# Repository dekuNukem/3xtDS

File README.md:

3xtDS
=====

The 3DS Streaming Console with External Control Interface, or 3xtDS, is a modified Nintendo 3DS console equipped with an capture card and an USB interface that allows the control of buttons, circle pad, and touch screen from an external source, as well as streaming high quality video of the content of both screen and sound back to the host to be recorded, or broadcast. This allows some very interesting applications such as interactive streaming on Twitch or other websites, gameplay automation, remote play over Internet, using alternative controllers, and much more.

Please see a short video of it in action: https://www.youtube.com/watch?v=9PZrJH7Z8KE

I want to thank u/velocikoopa for providing a console for me to work on, without him this project would be impossible.

Project gallery: http://imgur.com/a/ICxh5

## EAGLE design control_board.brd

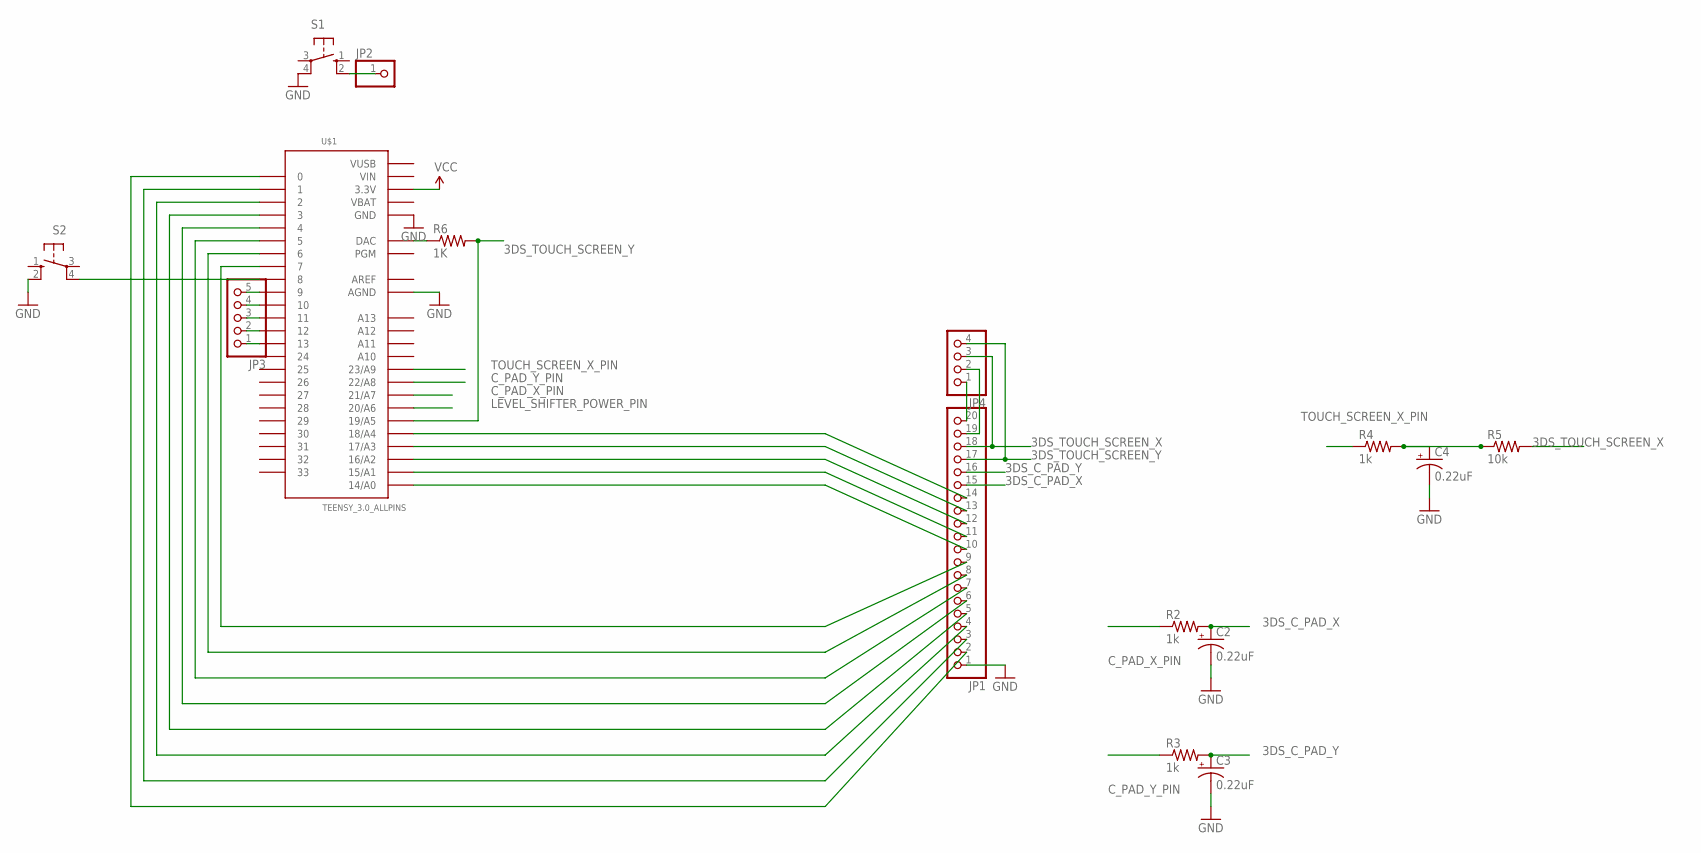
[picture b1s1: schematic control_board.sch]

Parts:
C2, C3, C4: 0.22uF; CPOL-RADIAL-10UF-25V
JP1: PINHD-1X20; 1X20
JP2: PINHD-1X1; 1X01
JP3: PINHD-1X5; 1X05
JP4: PINHD-1X4; 1X04
R2, R3, R4: 1k; 0207/7
R5: 10k; AXIAL-0.1
R6: 1K; 0207/7
S1, S2: 10-XX; B3F-10XX
U$1: TEENSY_3.0_ALLPINS

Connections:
3DS_C_PAD_X: C2.1 (+), JP1.15, R2.2
3DS_C_PAD_Y: C3.1 (+), JP1.16, R3.2
3DS_TOUCH_SCREEN_X: JP1.18, JP4.3, R5.P$2 (2)
3DS_TOUCH_SCREEN_Y: JP1.17, JP4.4, R6.2, U$1.19/A5
AREF: U$1.AREF
C_PAD_X_PIN: R2.1, U$1.21/A7
C_PAD_Y_PIN: R3.1, U$1.22/A8
GND: C2.2 (-), C3.2 (-), C4.2 (-), JP1.1, S1.4 (P1), S2.2 (S1), U$1.AGND, U$1.GND, U$1.GND1 (GND), U$1.GND2 (GND)
LEVEL_SHIFTER_POWER_PIN: U$1.20/A6
N0: C4.1 (+), R4.2, R5.P$1 (1)
unnamed: JP2.1, S1.2 (S1)
unnamed: JP1.10, U$1.14/A0
unnamed: JP1.11, U$1.15/A1
unnamed: JP1.12, U$1.16/A2
unnamed: JP1.13, U$1.17/A3
unnamed: JP1.2, U$1.0
unnamed: JP1.3, U$1.1
unnamed: JP1.4, U$1.2
unnamed: JP1.5, U$1.3
unnamed: JP1.6, U$1.4
unnamed: JP1.7, U$1.5
unnamed: JP1.8, U$1.6
unnamed: JP1.9, U$1.7
unnamed: R6.1, U$1.RESET (DAC)
unnamed: JP1.14, U$1.18/A4
unnamed: JP3.5, U$1.9
unnamed: JP3.4, U$1.10
unnamed: JP3.3, U$1.11
unnamed: JP3.2, U$1.12
unnamed: JP3.1, U$1.13
unnamed: JP1.20, JP4.1
unnamed: JP1.19, JP4.2
unnamed: S2.4 (P1), U$1.8
TOUCH_SCREEN_X_PIN: R4.1, U$1.23/A9
VBAT: U$1.VBAT
VCC: U$1.3.3V, U$1.3.3V1 (3.3V), U$1.3.3V2 (3.3V)
VIN: U$1.VIN
VUSB: U$1.VUSB

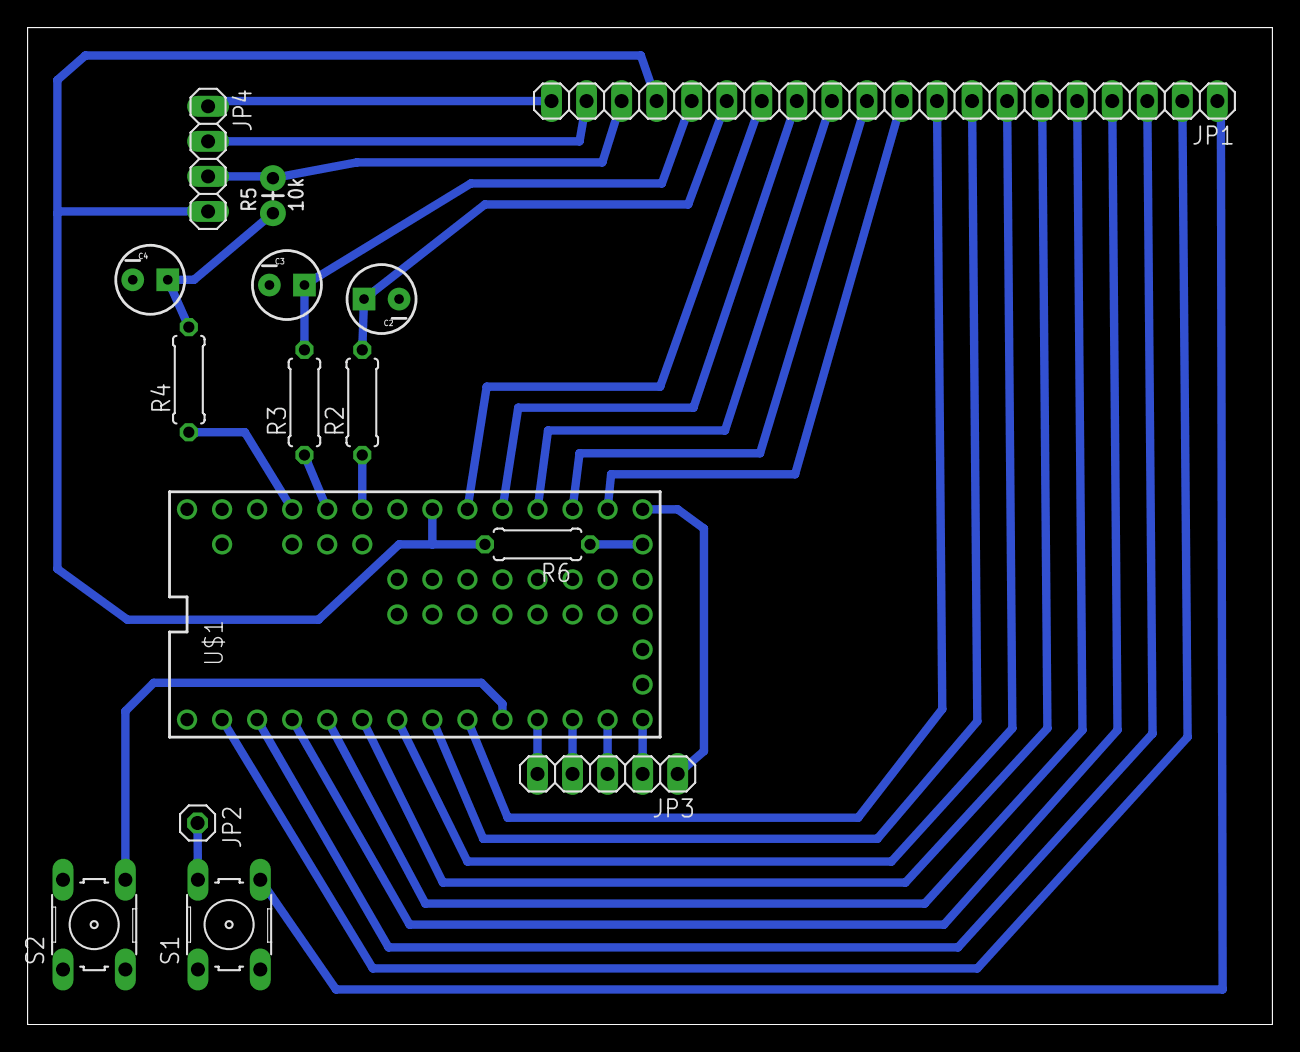
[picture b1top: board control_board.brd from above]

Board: 2 copper layers, 90.2 x 72.3 mm, 15 parts (0 on the bottom side), 33 nets.

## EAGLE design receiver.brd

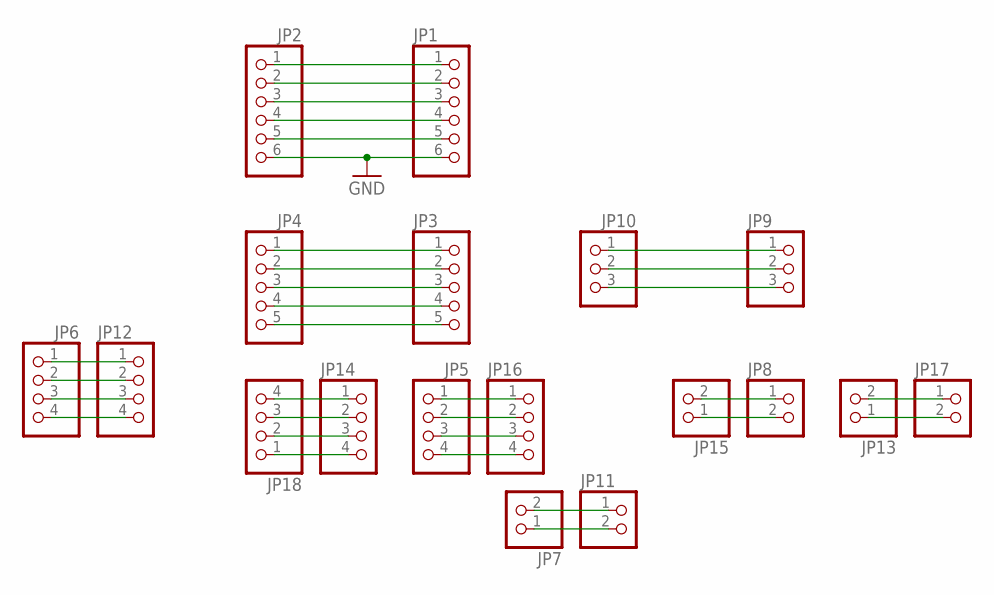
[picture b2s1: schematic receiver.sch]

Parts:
JP1, JP2: PINHD-1X6; 1X06
JP3, JP4: PINHD-1X5; 1X05
JP5, JP6, JP12, JP14, JP16, JP18: PINHD-1X4; 1X04
JP7, JP8, JP11, JP13, JP15, JP17: PINHD-1X2; 1X02
JP9, JP10: PINHD-1X3; 1X03

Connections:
GND: JP1.6, JP2.6
unnamed: JP1.1, JP2.1
unnamed: JP1.2, JP2.2
unnamed: JP1.3, JP2.3
unnamed: JP1.4, JP2.4
unnamed: JP1.5, JP2.5
unnamed: JP8.1, JP15.2
unnamed: JP3.1, JP4.1
unnamed: JP3.2, JP4.2
unnamed: JP3.3, JP4.3
unnamed: JP3.4, JP4.4
unnamed: JP3.5, JP4.5
unnamed: JP8.2, JP15.1
unnamed: JP7.2, JP11.1
unnamed: JP7.1, JP11.2
unnamed: JP6.1, JP12.1
unnamed: JP6.2, JP12.2
unnamed: JP6.3, JP12.3
unnamed: JP6.4, JP12.4
unnamed: JP5.1, JP16.1
unnamed: JP9.1, JP10.1
unnamed: JP9.2, JP10.2
unnamed: JP9.3, JP10.3
unnamed: JP5.2, JP16.2
unnamed: JP5.3, JP16.3
unnamed: JP5.4, JP16.4
unnamed: JP14.1, JP18.4
unnamed: JP14.2, JP18.3
unnamed: JP14.3, JP18.2
unnamed: JP14.4, JP18.1
unnamed: JP13.2, JP17.1
unnamed: JP13.1, JP17.2

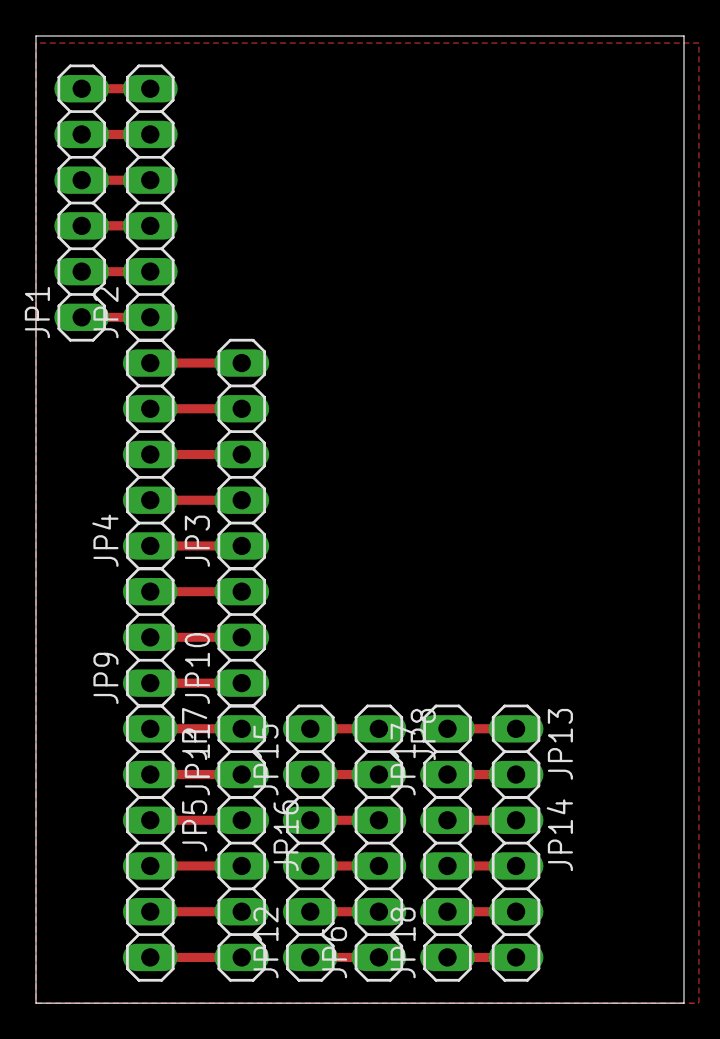
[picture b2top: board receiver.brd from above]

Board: 2 copper layers, 36.0 x 53.7 mm, 18 parts (0 on the bottom side), 32 nets.

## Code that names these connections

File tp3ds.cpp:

#include <stdint.h>
#include <stdio.h>
#define BUTTON_A_PIN 0
#define BUTTON_B_PIN 1
#define BUTTON_X_PIN 2
#define BUTTON_Y_PIN 3
#define BUTTON_RIGHT_SHOULDER_PIN 4
#define BUTTON_LEFT_SHOULDER_PIN 5
#define BUTTON_UP_PIN 6
#define BUTTON_DOWN_PIN 7
#define BUTTON_LEFT_PIN 14
#define BUTTON_RIGHT_PIN 15
#define BUTTON_START_PIN 16
#define BUTTON_SELECT_PIN 17
#define BUTTON_HOME_PIN 18
#define TOUCH_SCREEN_X_PIN 23
#define TOUCH_SCREEN_Y_PIN A14
#define TOUCH_SCREEN_Y_SENSE_PIN 19
#define C_PAD_X_PIN 21
#define C_PAD_Y_PIN 22
#define DEBUG_BUTTON_PIN 8
#define LED_PIN 13
#define C_PAD_DEFAULT_POTENTIAL 140
#define DAC_9_BIT_1V8 279
#define RECV_BUF_SIZE 64
#define BUTTON_PRESSED LOW
#define MINIMAL_DELAY_MS 10

char recv_buf[RECV_BUF_SIZE];
int32_t c_pad_nudge_delay_ms;
int32_t button_click_delay_ms;
int32_t touch_screen_click_delay_ms;

void setup()
{
	// Teensy USB serial always run at full USB speed of 12 Mbit/sec,
	// regardless of the argument.
    Serial.begin(9600);
    analogWriteResolution(9);
	analogReadResolution(10);
	// PWM frequency at 90KHz
	analogWriteFrequency(TOUCH_SCREEN_X_PIN, 90000);
	pinMode(DEBUG_BUTTON_PIN, INPUT_PULLUP);
	delay(1);
	pinMode(LED_PIN, OUTPUT);
	pinMode(BUTTON_A_PIN, OUTPUT);
	pinMode(BUTTON_B_PIN, OUTPUT);
	pinMode(BUTTON_X_PIN, OUTPUT);
	pinMode(BUTTON_Y_PIN, OUTPUT);
	pinMode(BUTTON_RIGHT_SHOULDER_PIN, OUTPUT);
	pinMode(BUTTON_LEFT_SHOULDER_PIN, OUTPUT);
	pinMode(BUTTON_UP_PIN, OUTPUT);
	pinMode(BUTTON_DOWN_PIN, OUTPUT);
	pinMode(BUTTON_LEFT_PIN, OUTPUT);
	pinMode(BUTTON_RIGHT_PIN, OUTPUT);
	pinMode(BUTTON_START_PIN, OUTPUT);
	pinMode(BUTTON_SELECT_PIN, OUTPUT);
	pinMode(BUTTON_HOME_PIN, OUTPUT);
	button_release_all();
	pinMode(C_PAD_X_PIN, OUTPUT);
	pinMode(C_PAD_Y_PIN, OUTPUT);
	c_pad_reset();
	button_click_delay_ms = 250;
    c_pad_nudge_delay_ms = 500;
    touch_screen_click_delay_ms = 100;
    digitalWrite(LED_PIN, HIGH);
    while(digitalRead(DEBUG_BUTTON_PIN) == HIGH)
    	Serial.read();
    digitalWrite(LED_PIN, LOW);
    pinMode(TOUCH_SCREEN_X_PIN, OUTPUT);
	pinMode(TOUCH_SCREEN_Y_PIN, OUTPUT);
    analogWrite(TOUCH_SCREEN_X_PIN, 0);
    disable_touch_screen();
}

// main loop, wait for commands from PC
void loop()
{
	if(get_serial_command(recv_buf, RECV_BUF_SIZE) != -1)
	{
		// c-pad nudge:  cn 127 240
		if(strncmp(recv_buf, "cn ", 3) == 0)
		{
			int16_t arg1_pos = goto_next_arg(0, recv_buf, RECV_BUF_SIZE);
			int16_t arg2_pos = goto_next_arg(arg1_pos, recv_buf, RECV_BUF_SIZE);
			int16_t x = atoi(recv_buf + arg1_pos);
			int16_t y = atoi(recv_buf + arg2_pos);
			c_pad_nudge(x, y, c_pad_nudge_delay_ms);
		}
		// c-pad hold: ch 127 240
		if(strncmp(recv_buf, "ch ", 3) == 0)
		{
			int16_t arg1_pos = goto_next_arg(0, recv_buf, RECV_BUF_SIZE);
			int16_t arg2_pos = goto_next_arg(arg1_pos, recv_buf, RECV_BUF_SIZE);
			int16_t x = atoi(recv_buf + arg1_pos);
			int16_t y = atoi(recv_buf + arg2_pos);
			c_pad_hold(x, y);
		}
		// c-pad release: cr
		if(strncmp(recv_buf, "cr\n", 3) == 0)
			c_pad_reset();
		/*	
		c-pad set nudge delay, aka how long the c-pad
		is held before releasing when c_pad_nudge is called
		cd 100
		*/
		if(strncmp(recv_buf, "cd ", 3) == 0)
		{
			int16_t arg1_pos = goto_next_arg(0, recv_buf, RECV_BUF_SIZE);
			int16_t new_delay = atoi(recv_buf + arg1_pos);
			new_delay > MINIMAL_DELAY_MS ? c_pad_nudge_delay_ms = new_delay : c_pad_nudge_delay_ms;
		}
		// touch screen click: tc 120 50
		if(strncmp(recv_buf, "tc ", 3) == 0)
		{
			int16_t arg1_pos = goto_next_arg(0, recv_buf, RECV_BUF_SIZE);
			int16_t arg2_pos = goto_next_arg(arg1_pos, recv_buf, RECV_BUF_SIZE);
			int16_t x = atoi(recv_buf + arg1_pos);
			int16_t y = atoi(recv_buf + arg2_pos);
			touch_screen_click(x, y, touch_screen_click_delay_ms);
		}
		// touch screen set click delay in ms: td 100
		if(strncmp(recv_buf, "td ", 3) == 0)
		{
			int16_t arg1_pos = goto_next_arg(0, recv_buf, RECV_BUF_SIZE);
			int16_t new_delay = atoi(recv_buf + arg1_pos);
			new_delay > MINIMAL_DELAY_MS ? touch_screen_click_delay_ms = new_delay : touch_screen_click_delay_ms;
		}
		// button click: bc a
		if(strncmp(recv_buf, "bc ", 3) == 0)
		{
			int16_t arg1_pos = goto_next_arg(0, recv_buf, RECV_BUF_SIZE);
			button_click(get_button_pin(recv_buf + arg1_pos), button_click_delay_ms);
		}
		// button hold: bh a
		if(strncmp(recv_buf, "bh ", 3) == 0)
		{
			int16_t arg1_pos = goto_next_arg(0, recv_buf, RECV_BUF_SIZE);
			button_press(get_button_pin(recv_buf + arg1_pos));
		}
		// button release: br a
		if(strncmp(recv_buf, "br ", 3) == 0)
		{
			int16_t arg1_pos = goto_next_arg(0, recv_buf, RECV_BUF_SIZE);
			button_release(get_button_pin(recv_buf + arg1_pos));
		}
		// button release all: br\n
		if(strncmp(recv_buf, "br\n", 3) == 0)
			button_release_all();

		// button set click delay in ms: bd 100
		if(strncmp(recv_buf, "bd ", 3) == 0)
		{
			int16_t arg1_pos = goto_next_arg(0, recv_buf, RECV_BUF_SIZE);
			int16_t new_delay = atoi(recv_buf + arg1_pos);
			new_delay > MINIMAL_DELAY_MS ? button_click_delay_ms = new_delay : button_click_delay_ms;
		}
	}
}

void button_click(int8_t button_pin, int16_t button_delay)
{
	button_press(button_pin);
	delay(button_delay);
	button_release(button_pin);
	delay(20);
}

void button_press(int8_t button_pin)
{
	pinMode(button_pin, OUTPUT);
	digitalWrite(button_pin, BUTTON_PRESSED);
}

void button_release(int8_t button_pin)
{
	pinMode(button_pin, INPUT);
}

void button_release_all()
{
	button_release(BUTTON_A_PIN);
	button_release(BUTTON_B_PIN);
	button_release(BUTTON_X_PIN);
	button_release(BUTTON_Y_PIN);
	button_release(BUTTON_RIGHT_SHOULDER_PIN);
	button_release(BUTTON_LEFT_SHOULDER_PIN);
	button_release(BUTTON_UP_PIN);
	button_release(BUTTON_DOWN_PIN);
	button_release(BUTTON_LEFT_PIN);
	button_release(BUTTON_RIGHT_PIN);
	button_release(BUTTON_START_PIN);
	button_release(BUTTON_SELECT_PIN);
	button_release(BUTTON_HOME_PIN);
}

int32_t goto_next_arg(int16_t current_pos, char* buf, int16_t size)
{
	while(current_pos < size && buf[current_pos] != ' ')
		current_pos++;

	while(current_pos < size && buf[current_pos] == ' ')
		current_pos++;
	return current_pos;
}

// get a complete command from serial
int8_t get_serial_command(char buf[], int16_t size)
{
	if(Serial.available())
	{
		int16_t count = 0;
		memset(buf, 0, size);
		char c;
		while(1)
			if(Serial.available())
			{
				c = Serial.read();
				// ignore carriage return
				if(c == '\r')
					continue;
				if(count < size - 1)
					buf[count] = c;
				count++;
				if(c == '\n')
					return 0;
			}
	}
	else
		return -1;
}

void c_pad_nudge(uint16_t x, uint16_t y, int16_t duration_ms)
{
	c_pad_hold(x, y);
	delay(duration_ms);
	c_pad_reset();
}

void c_pad_hold(uint16_t x, uint16_t y)
{
	if(x > 255 || y > 255)
		return;
	analogWrite(C_PAD_X_PIN, x);
	analogWrite(C_PAD_Y_PIN, y);
}

void c_pad_reset()
{
	analogWrite(C_PAD_X_PIN, C_PAD_DEFAULT_POTENTIAL);
	analogWrite(C_PAD_Y_PIN, C_PAD_DEFAULT_POTENTIAL);
}

void touch_screen_click(uint16_t x, uint16_t y, int16_t duration_ms)
{
	if(x <= 0 || y <= 0 || x > 320 || y > 240)
		return;
	int16_t x_potential = ((double)x / 320) * 320;
	int16_t y_potential = ((double)y / 240) * 320;
	
	y_potential -= (((double)(y_potential)) * 0.257 - 29);
	x_potential -= (((double)(x_potential)) * 0.066 - 7);

	analogWrite(TOUCH_SCREEN_X_PIN, x_potential);
	enable_touch_screen();
	int32_t start = millis();
	while(millis() - start < duration_ms)
	{
		// wait until Y+ pin is in output mode
		while(analogRead(TOUCH_SCREEN_Y_SENSE_PIN) < 512);
		delayMicroseconds(490);
		// now Y+ pin is in input mode, write the value
		analogWrite(TOUCH_SCREEN_Y_PIN, y_potential);
		delayMicroseconds(180);
		// pull Y+ down again to keep interrupt going
		enable_touch_screen();
	}
	disable_touch_screen();
	analogWrite(TOUCH_SCREEN_X_PIN, 0);
	delay(50);
}

void disable_touch_screen()
{
	analogWrite(TOUCH_SCREEN_Y_PIN, DAC_9_BIT_1V8);
}

// pull Y+ pin low to initialize 3DS's touch interrupt
void enable_touch_screen()
{
	analogWrite(TOUCH_SCREEN_Y_PIN, 0);
}

int8_t get_button_pin(char* buf)
{
	if(strncmp(buf, "a\n", 2) == 0)
		return BUTTON_A_PIN;
	if(strncmp(buf, "b\n", 2) == 0)
		return BUTTON_B_PIN;
	if(strncmp(buf, "x\n", 2) == 0)
		return BUTTON_X_PIN;
	if(strncmp(buf, "y\n", 2) == 0)
		return BUTTON_Y_PIN;
	// right shoulder
	if(strncmp(buf, "rs\n", 3) == 0)
		return BUTTON_RIGHT_SHOULDER_PIN;
	// left shoulder
	if(strncmp(buf, "ls\n", 3) == 0)
		return BUTTON_LEFT_SHOULDER_PIN;
	if(strncmp(buf, "u\n", 2) == 0)
		return BUTTON_UP_PIN;
	if(strncmp(buf, "d\n", 2) == 0)
		return BUTTON_DOWN_PIN;
	if(strncmp(buf, "l\n", 2) == 0)
		return BUTTON_LEFT_PIN;
	if(strncmp(buf, "r\n", 2) == 0)
		return BUTTON_RIGHT_PIN;
	// start
	if(strncmp(buf, "st\n", 3) == 0)
		return BUTTON_START_PIN;
	// select
	if(strncmp(buf, "sl\n", 3) == 0)
		return BUTTON_SELECT_PIN;
	// home
	if(strncmp(buf, "h\n", 2) == 0)
		return BUTTON_HOME_PIN;
	else
		return -1;
}

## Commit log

2014-05-09 removed .DS_Store
2014-05-09 README update
2014-05-09 updated description
2014-06-12 schematic update
2014-07-26 “optimization”

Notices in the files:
parts and their libraries:
SparkFun-Capacitors: Licensing: Creative Commons ShareAlike 4.0 International - https://creativecommons.org/licenses/by-sa/4.0
